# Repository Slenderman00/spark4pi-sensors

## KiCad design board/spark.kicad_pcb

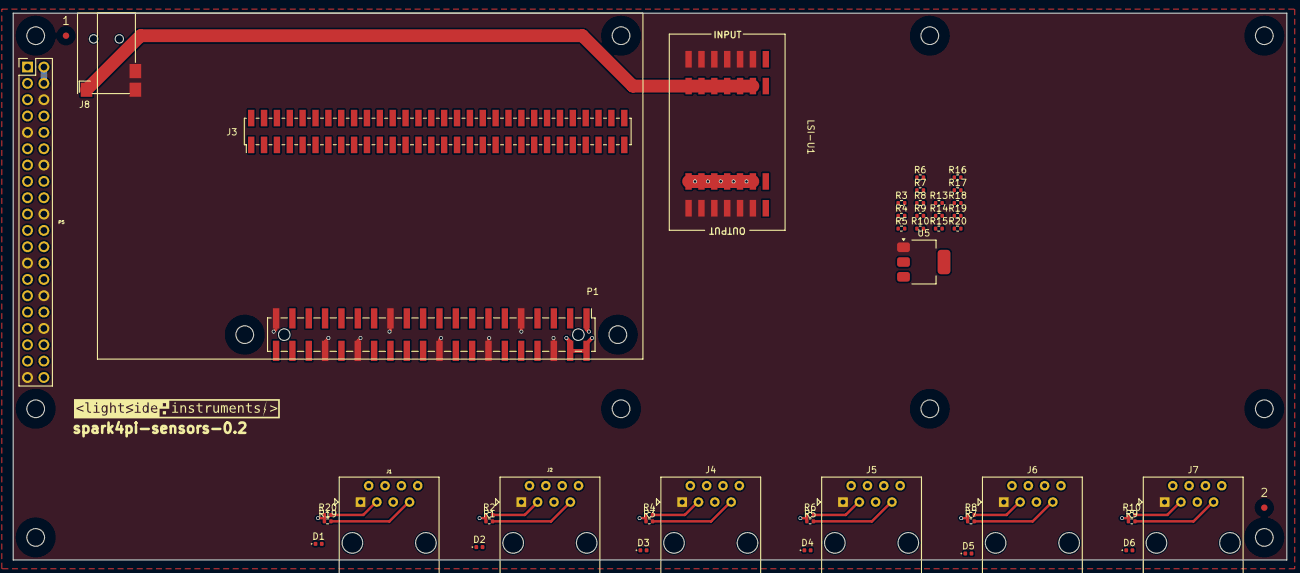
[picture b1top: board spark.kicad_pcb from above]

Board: 4 copper layers, 198.0 x 85.0 mm, 48 parts (0 on the bottom side), 55 nets.

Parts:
1, 2: (no value)
D1, D2, D3, D4, D5, D6: LED; LED_0402_1005Metric
J1, J2, J4, J5, J6, J7: RJ45; RJ45_Amphenol_54602-x08_Horizontal
J3: Conn_02x30_Odd_Even; PinHeader_2x30_P2.00mm_Vertical_SMD
J8: Barrel_Jack; PJ1-021-SMT-TR
LSI-U1: lsi-powermodule-7
P1: Conn_02x20_Odd_Even; PinSocket_2x20_P2.54mm_Vertical_Inverted_SMD_Alignment_Pin
P5: Raspberry_Pi_2_3; PinHeader_2x20_P2.54mm_Vertical_1_04mm
R1, R2, R3, R3#2, R4, R4#2, R5, R5#2, R6, R6#2, R7, R7#2, R8, R8#2, R9, R9#2, R10, R10#2, R19, R19#2, R20, R20#2: 4.7k; R_0402_1005Metric
R13, R14, R15, R16, R17, R18: 1K; R_0402_1005Metric
U5: LD1117S33TR_SOT223; SOT-223-3_TabPin2

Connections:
+3V3: J1.5, J2.5, J4.5, J5.5, J6.5, J7.5, P1.1, P1.17, P5.1 (3V3), P5.17 (3V3), R1.1, R2.1, R3.1, R3#2.1, R4.1, R4#2.1, R5.1, R5#2.1, R6.1, R6#2.1, R7.1, R7#2.1, R8.1, R8#2.1, R9.1, R9#2.1, R10.1, R10#2.1, R13.1, R14.1, R15.1, R16.1, R17.1, R18.1, R19.1, R19#2.1, R20.1, R20#2.1, U5.2 (VO)
+5V: LSI-U1.3 (VPP_OUT), P1.2, P1.4, P5.2 (5V), P5.4 (5V), U5.3 (VI)
GND: J1.1, J2.1, J4.1, J5.1, J6.1, J7.1, J8.2, J8.3, LSI-U1.1 (GND), LSI-U1.4 (GND), P1.6, P1.9, P1.14, P1.20, P1.25, P1.30, P1.34, P1.39, P5.6 (GND), P5.9 (GND), P5.14 (GND), P5.20 (GND), P5.25 (GND), P5.30 (GND), P5.34 (GND), P5.39 (GND), U5.1 (GND)
GPIO0: P1.27, P5.27 (ID_SD/GPIO0)
GPIO1: P1.28, P5.28 (ID_SC/GPIO1)
GPIO2: P1.3, P5.3 (SDA/GPIO2)
GPIO3: P1.5, P5.5 (SCL/GPIO3)
GPIO4: P1.7, P5.7 (GCLK0/GPIO4)
GPIO5: P1.29, P5.29 (GCLK1/GPIO5)
GPIO6: P1.31, P5.31 (GCLK2/GPIO6)
GPIO7: P1.26, P5.26 (~CE1/GPIO7)
GPIO12: P1.32, P5.32 (PWM0/GPIO12)
GPIO13: P1.33, P5.33 (PWM1/GPIO13)
GPIO14: P1.8, P5.8 (GPIO14/TXD)
GPIO15: P1.10, P5.10 (GPIO15/RXD)
GPIO16: P1.36, P5.36 (GPIO16)
GPIO17: P1.11, P5.11 (GPIO17)
GPIO18: P1.12, P5.12 (GPIO18/PWM0)
GPIO19: P1.35, P5.35 (GPIO19/MISO1)
GPIO20: P1.38, P5.38 (GPIO20/MOSI1)
GPIO21: P1.40, P5.40 (GPIO21/SCLK1)
GPIO22: P1.15, P5.15 (GPIO22)
GPIO23: P1.16, P5.16 (GPIO23)
GPIO26: P1.37, P5.37 (GPIO26)
GPIO27: P1.13, P5.13 (GPIO27)
LED_0: D1.1 (K), J3.2
LED_1: D2.1 (K), J3.4
LED_2: D3.1 (K), J3.6
LED_3: D4.1 (K), J3.8
LED_4: D5.1 (K), J3.10
LED_5: D6.1 (K), J3.12
MISO: P1.21, P5.21 (MISO0/GPIO9)
MOSI: P1.19, P5.19 (MOSI0/GPIO10)
unnamed: D1.2 (A), R13.2
unnamed: D2.2 (A), R14.2
unnamed: D3.2 (A), R15.2
unnamed: D4.2 (A), R16.2
unnamed: D5.2 (A), R17.2
unnamed: D6.2 (A), R18.2
SCK: P1.23, P5.23 (SCLK0/GPIO11)
SCL_0: J1.3, J3.3, R20.2, R20#2.2
SCL_1: J2.3, J3.7, R2.2
SCL_2: J3.11, J4.3, R4.2, R4#2.2
SCL_3: J3.15, J5.3, R6.2, R6#2.2
SCL_4: J3.19, J6.3, R8.2, R8#2.2
SCL_5: J3.23, J7.3, R10.2, R10#2.2
SDA_0: J1.7, J3.1, R19.2, R19#2.2
SDA_1: J2.7, J3.5, R1.2
SDA_2: J3.9, J4.7, R3.2, R3#2.2
SDA_3: J3.13, J5.7, R5.2, R5#2.2
SDA_4: J3.17, J6.7, R7.2, R7#2.2
SDA_5: J3.21, J7.7, R9.2, R9#2.2
SYS_DCIN: J8.1, LSI-U1.2 (VPP_IN)
iCE_CDONE: P1.22, P5.22 (GPIO25)
iCE_SS_B: P1.24, P5.24 (~CE0/GPIO8)

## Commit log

2025-01-11 stuff
2025-01-11 fix: added correct i2c busses
2025-01-12 feat: added pull ups
2025-01-12 feat: initial board stuff
2025-01-12 fix: moved mosfets down
2025-01-12 feat: connected mosfets
2025-01-12 feat: updated version number
2025-01-13 feat: inital version
2025-01-13 feat: breaking up longer traces
2025-01-13 feat: workflow for exporting of images
2025-01-13 fix: workflow
2025-01-13 feat: added images folder
2025-01-13 fix: moving images to correct folder
2025-01-13 fix: removed dependency
2025-01-13 feat: commit instead of artifact
2025-01-13 fix: added images to gitignore
2025-01-13 feat: render images
2025-01-13 fix: uploading all images
2025-01-13 fix: no images in gitignore
2025-01-13 feat: added secret token
2025-01-13 feat: git auto commit workflow
2025-01-13 Apply automatic changes
2025-01-13 fix: fixed need
2025-01-13 feat: add sleep
2025-01-13 feat: removed line
2025-01-14 feat: rev 2
2025-01-14 fix: indentation
2025-01-14 feat: pulling remote changes
